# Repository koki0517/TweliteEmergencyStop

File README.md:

# TweliteEmergencyStop
Tweliteを使った遠隔非常停止

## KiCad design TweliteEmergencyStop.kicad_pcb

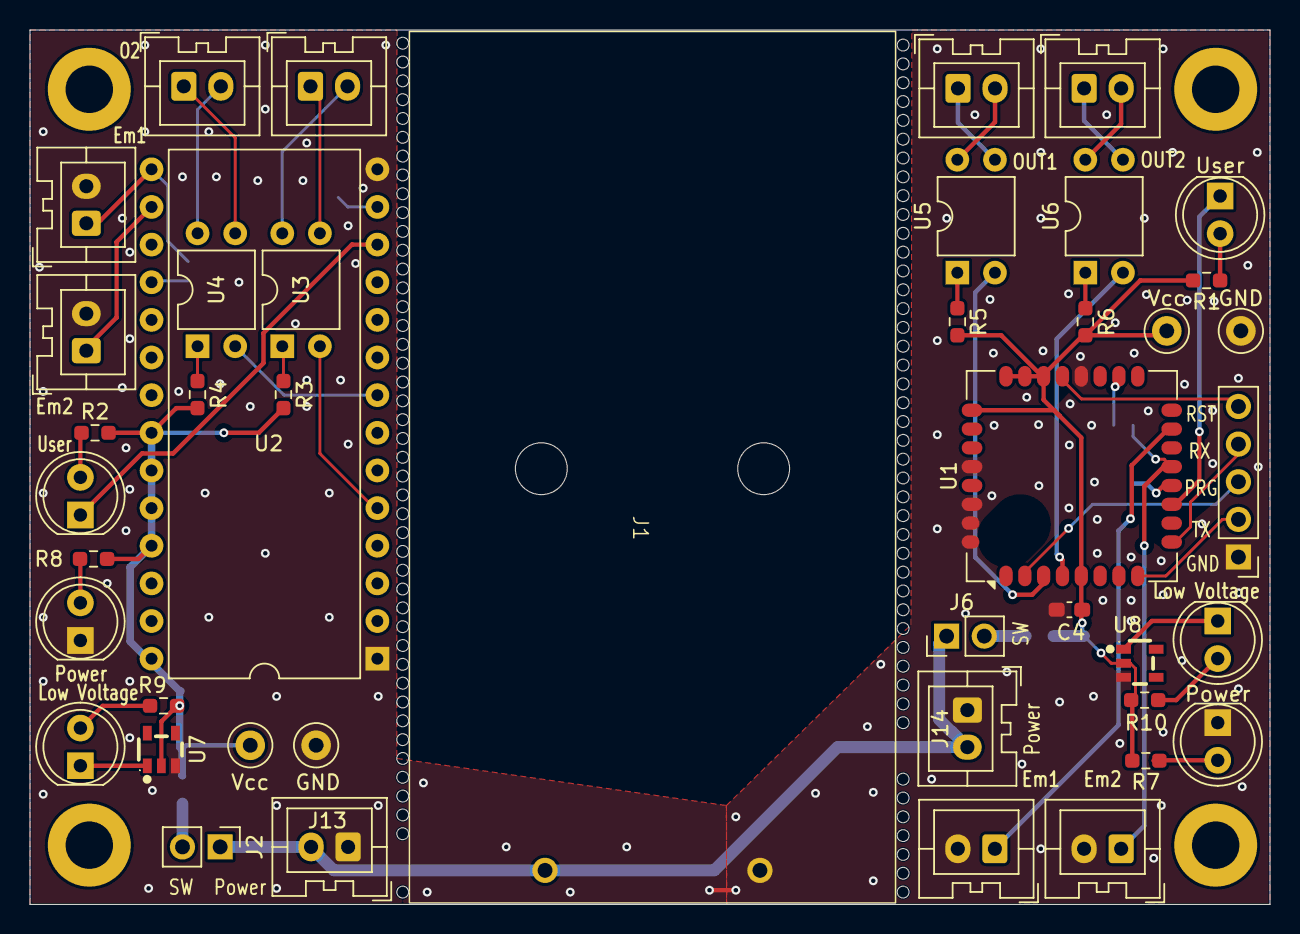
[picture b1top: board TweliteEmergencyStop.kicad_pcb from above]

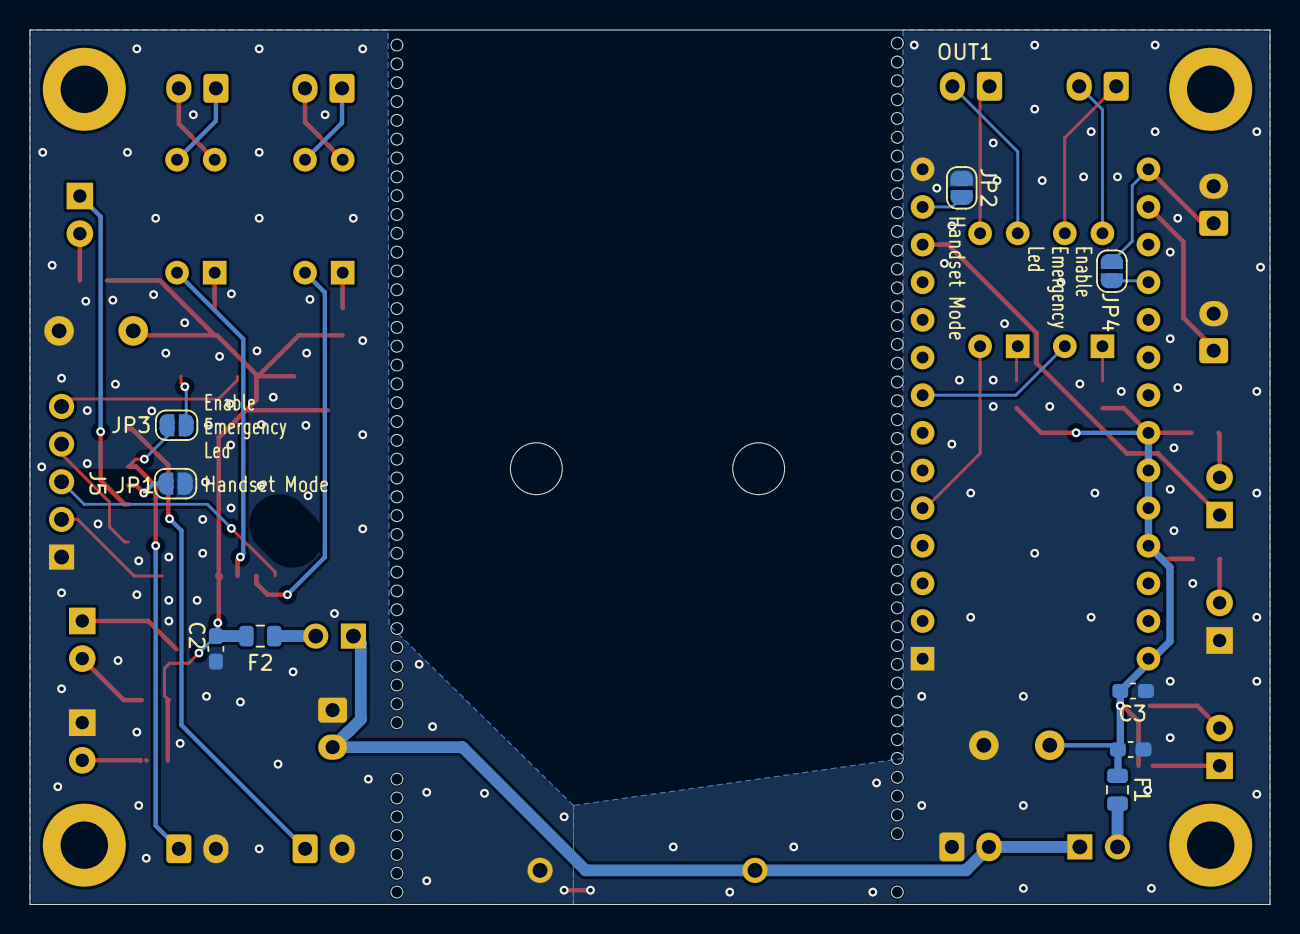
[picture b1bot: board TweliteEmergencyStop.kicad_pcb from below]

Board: 2 copper layers, 83.7 x 59.0 mm, 52 parts (9 on the bottom side), 43 nets.

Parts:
C1, C2: 1u; C_0603_1608Metric_Pad1.08x0.95mm_HandSolder
C3, C4: 100n; C_0603_1608Metric_Pad1.08x0.95mm_HandSolder
Em1: Emergency2; JST_XA_B02B-XASK-1_1x02_P2.50mm_Vertical
Em1#2, Em2: Emergency; JST_XA_B02B-XASK-1_1x02_P2.50mm_Vertical
Em2#2: Emergency1; JST_XA_B02B-XASK-1_1x02_P2.50mm_Vertical
F1, F2: 350mA; Fuse_0805_2012Metric
GND: GND; TestPoint_Loop_D1.80mm_Drill1.0mm_Beaded
GND#2: GND; TestPoint_Loop_D1.80mm_Drill1.0mm_Beaded
J1: BatteryBox; batterybox
J2, J6: Conn_01x02_Pin; PinHeader_1x02_P2.54mm_Vertical
J5: Program; PinHeader_1x05_P2.54mm_Vertical
J13, J14: XA02; JST_XA_B02B-XASK-1_1x02_P2.50mm_Vertical
JP1, JP2: mode; SolderJumper-2_P1.3mm_Open_RoundedPad1.0x1.5mm
JP3, JP4: sw; SolderJumper-2_P1.3mm_Open_RoundedPad1.0x1.5mm
Low Voltage: btyLED; LED_D5.0mm
Low Voltage#2: btyLED; LED_D5.0mm
O2: XA02; JST_XA_B02B-XASK-1_1x02_P2.50mm_Vertical
OUT1, OUT1#2, OUT2: XA02; JST_XA_B02B-XASK-1_1x02_P2.50mm_Vertical
Power: pwrLED; LED_D5.0mm
Power#2: pwrLED; LED_D5.0mm
R1, R2, R7, R8, R9, R10: 500; R_0603_1608Metric_Pad0.98x0.95mm_HandSolder
R3, R4, R5, R6: 300; R_0603_1608Metric_Pad0.98x0.95mm_HandSolder
U1: TWE-L-WX; MonoWireless_TWE-L-WX
U2: TWE-L-DP-W; DIP-28_W15.24mm
U3, U4, U5, U6: PC817; DIP-4_W7.62mm
U7, U8: R3111N211A; SOT-23-5_L2.9-W1.6-P0.95-LS2.8-BR
User: usrLED; LED_D5.0mm
User#2: usrLED; LED_D5.0mm
Vcc: VCC; TestPoint_Loop_D1.80mm_Drill1.0mm_Beaded
Vcc#2: VCC; TestPoint_Loop_D1.80mm_Drill1.0mm_Beaded

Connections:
/DI1_1: Em1#2.1, JP4.1 (A), U2.15 (DIO12/DI1)
/DI1_2: Em2#2.1, JP3.1 (A), U1.13 (DIO12/DI1)
/DI2_1: Em2.1, U2.16 (DIO13/DI2)
/DI2_2: Em1.1, U1.15 (DIO13/DI2)
/DO1_1: U2.5 (DIO18/DO1), U3.2
/DO1_2: U1.3 (DIO18/DO1), U5.2
/DO2_1: U2.8 (DIO19/DO2), U4.2
/DO2_2: U1.4 (DIO19/DO2), U6.2
/PRG2: J5.3, U1.2 (DO1/PWM3)
/RST2: J5.5, U1.21 (~RESET)
/RX2: J5.4, U1.9 (DIO7/RX)
/TX2: J5.2, U1.8 (DIO6/TX)
/pwr: J1.2, J2.1, J6.1, J13.2, J14.2
GND: C1.2, C2.2, C3.2, C4.2, Em1.2, Em1#2.2, Em2.2, Em2#2.2, GND.1, GND#2.1, J1.1, J5.1, J13.1, J14.1, JP1.1 (A), JP2.1 (A), Power.1 (K), Power#2.1 (K), U1.20 (GND), U1.28 (GND), U1.30 (GND), U1.31 (GND), U1.32 (GND), U2.1 (GND), U2.14 (GND), U7.3 (GND), U8.3 (GND)
unnamed: R1.1, User#2.2 (A)
unnamed: U1.11 (DIO9/DO4), User#2.1 (K)
unnamed: R2.1, User.2 (A)
unnamed: U2.12 (DIO9/DO4), User.1 (K)
unnamed: Power.2 (A), R7.1
unnamed: Power#2.2 (A), R8.1
unnamed: Low Voltage#2.2 (A), R9.1
unnamed: Low Voltage#2.1 (K), U7.1 (OUT)
unnamed: Low Voltage.2 (A), R10.1
unnamed: Low Voltage.1 (K), U8.1 (OUT)
unnamed: F1.2, J2.2
unnamed: F2.2, J6.2
unnamed: OUT1#2.1, U5.3
unnamed: OUT1#2.2, U5.4
unnamed: OUT2.1, U6.3
unnamed: OUT2.2, U6.4
unnamed: OUT1.1, U3.3
unnamed: OUT1.2, U3.4
unnamed: O2.1, U4.3
unnamed: O2.2, U4.4
unnamed: JP1.2 (B), U1.12 (DIO10/M1)
unnamed: JP2.2 (B), U2.13 (DIO10/M1)
unnamed: JP3.2 (B), U1.18 (DIO16/DI4)
unnamed: JP4.2 (B), U2.18 (DIO16/DI4)
unnamed: R3.1, U3.1
unnamed: R4.1, U4.1
unnamed: R5.1, U5.1
unnamed: R6.1, U6.1
VCC: C1.1, C2.1, C3.1, C4.1, F1.1, F2.1, R1.2, R2.2, R3.2, R4.2, R5.2, R6.2, R7.2, R8.2, R9.2, R10.2, U1.5 (VCC), U1.22 (ADC2/AI3), U1.23 (ADC1/AI1), U1.24 (DIO0/AI2), U1.25 (DIO1/AI4), U2.22 (ADC1/AI1), U2.23 (DIO0/AI2), U2.24 (ADC2/AI3), U2.25 (DIO1/AI4), U2.28 (VCC), U7.2 (VDD), U8.2 (VDD), Vcc.1, Vcc#2.1

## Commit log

2025-11-04 バッテリーBOXのフットプリントの追加
2025-11-05 回路図どね
2025-11-05 ひらめいた
2025-11-05 Create LICENSE
